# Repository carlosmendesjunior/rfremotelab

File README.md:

# rfremotelab
**RF Remote Laboratory - ReLab**

This is a result of the post-doc of Carlos Mendes Jr. with the research assistance of Lino Van Mulken supported by Rainier van Dommele and idealized by Peter Baltus, all from Eindhoven University of Technology, The Netherlands.

We all hope that this work can help others around the world to disseminate RF laboratory experience among their students from university, college, or school.

We also welcome contributions from everyone! :)

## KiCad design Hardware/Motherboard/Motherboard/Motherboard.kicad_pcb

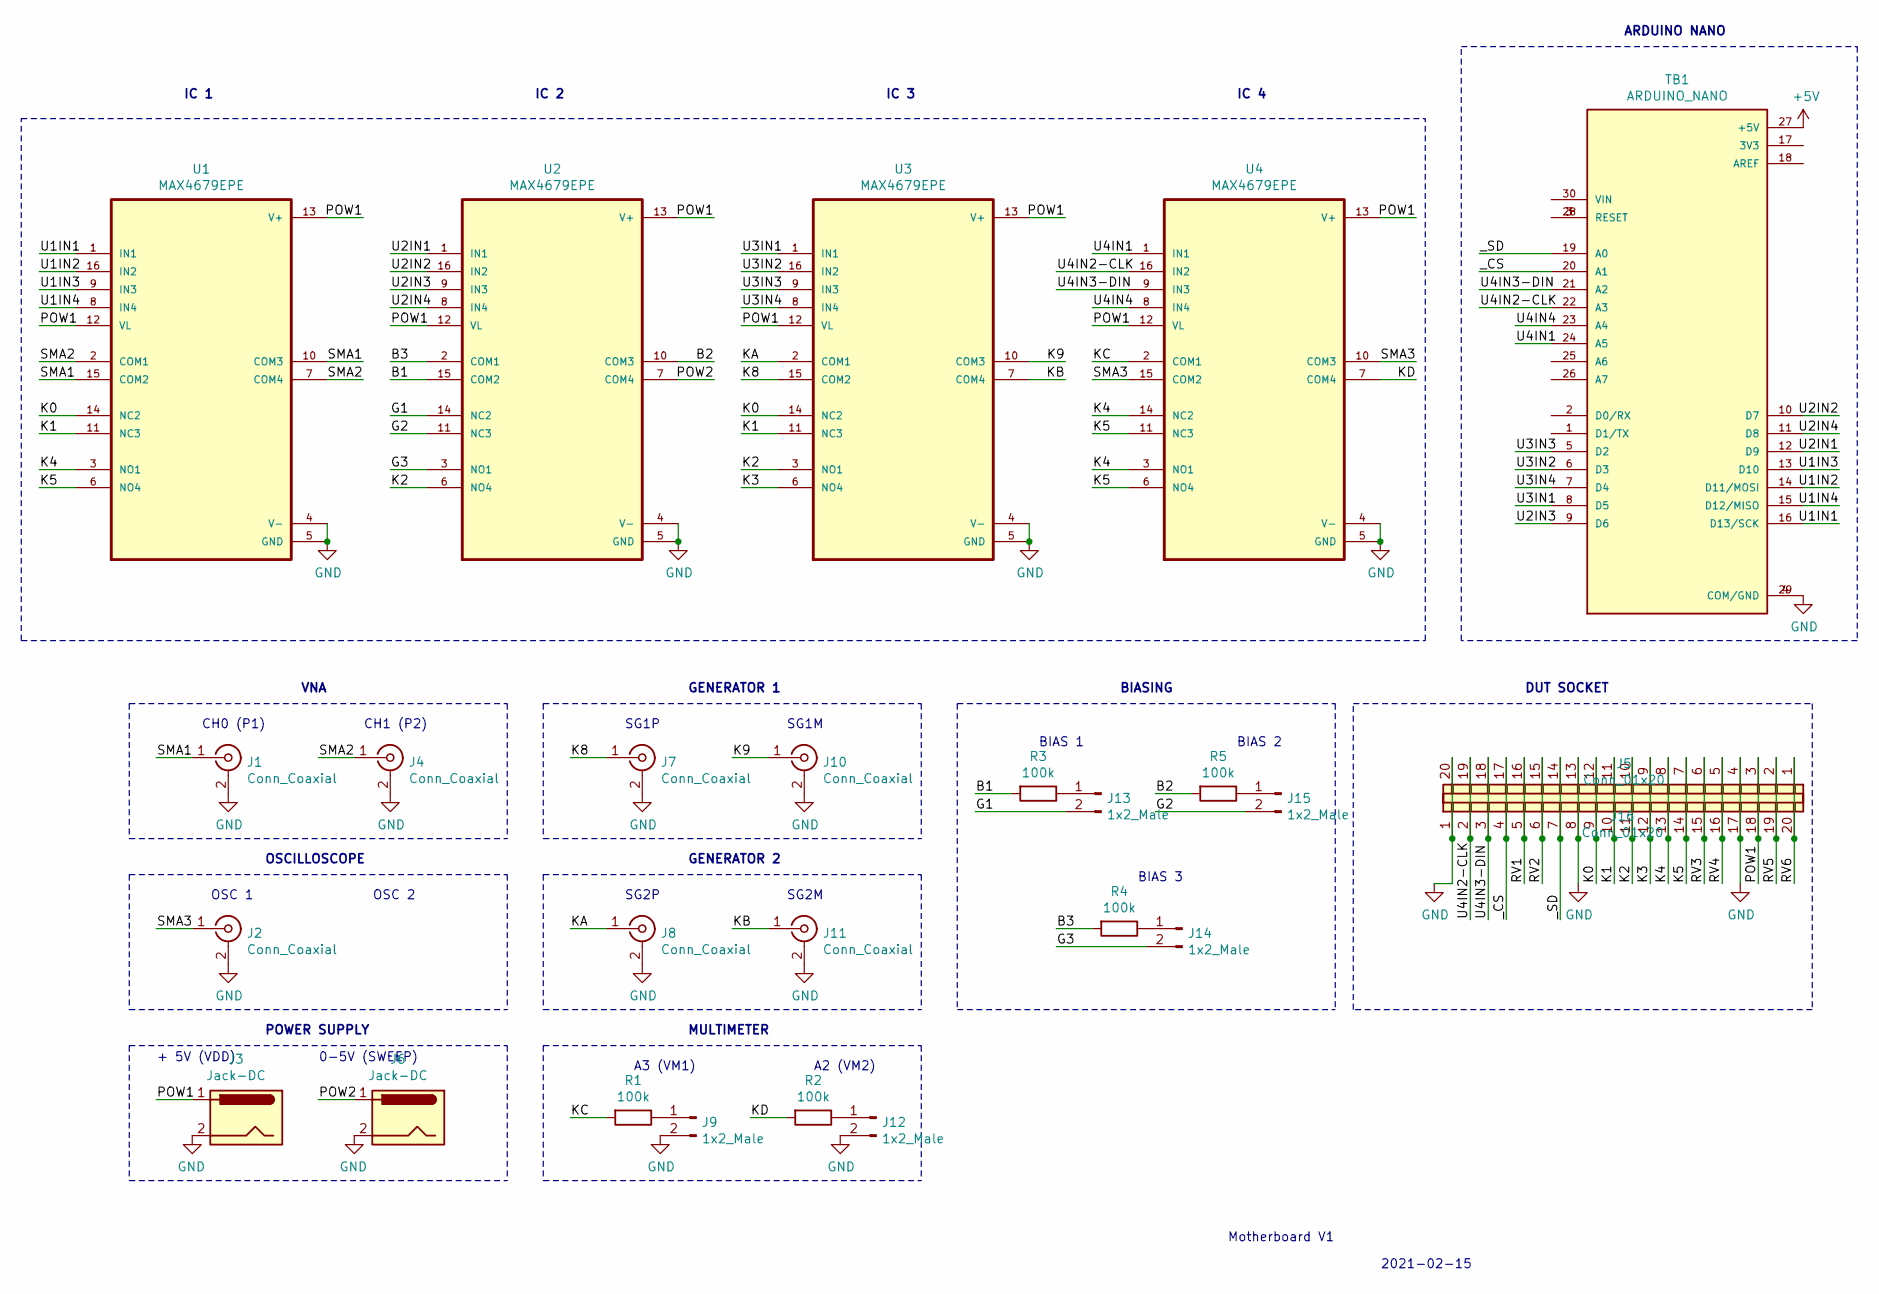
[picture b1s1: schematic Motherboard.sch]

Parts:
J1, J2, J4, J7, J8, J10, J11: Conn_Coaxial; SMA_Amphenol_132289_EdgeMount
J3, J6: Jack-DC; BarrelJack_Wuerth_6941xx301002
J5, J16: Conn_01x20; PinSocket_1x20_P2.54mm_Vertical
J9, J12, J13, J14, J15: 1x2_Male; PinHeader_1x02_P2.54mm_Vertical
R1, R2, R3, R4, R5: 100k; R_Axial_DIN0207_L6.3mm_D2.5mm_P10.16mm_Horizontal
TB1: ARDUINO_NANO; Arduino_Nano
U1, U2, U3, U4: MAX4679EPE; DIP-16_W7.62mm_LongPads

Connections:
+5V: TB1.27 (+5V)
/B1: R3.2, U2.15 (COM2)
/B2: R5.2, U2.10 (COM3)
/B3: R4.2, U2.2 (COM1)
/G1: J13.2, U2.14 (NC2)
/G2: J15.2, U2.11 (NC3)
/G3: J14.2, U2.3 (NO1)
/K0: J5.9, J16.12, U1.14 (NC2), U3.14 (NC2)
/K1: J5.10, J16.11, U1.11 (NC3), U3.11 (NC3)
/K2: J5.11, J16.10, U2.6 (NO4), U3.3 (NO1)
/K3: J5.12, J16.9, U3.6 (NO4)
/K4: J5.13, J16.8, U1.3 (NO1), U4.3 (NO1), U4.14 (NC2)
/K5: J5.14, J16.7, U1.6 (NO4), U4.6 (NO4), U4.11 (NC3)
/K8: J7.1 (In), U3.15 (COM2)
/K9: J10.1 (In), U3.10 (COM3)
/KA: J8.1 (In), U3.2 (COM1)
/KB: J11.1 (In), U3.7 (COM4)
/KC: R1.2, U4.2 (COM1)
/KD: R2.2, U4.7 (COM4)
/POW1: J3.1, J5.18, J16.3, U1.12 (VL), U1.13 (V+), U2.12 (VL), U2.13 (V+), U3.12 (VL), U3.13 (V+), U4.12 (VL), U4.13 (V+)
/POW2: J6.1, U2.7 (COM4)
/RV1: J5.5, J16.16
/RV2: J5.6, J16.15
/RV3: J5.15, J16.6
/RV4: J5.16, J16.5
/RV5: J5.19, J16.2
/RV6: J5.20, J16.1
/SMA1: J1.1 (In), U1.10 (COM3), U1.15 (COM2)
/SMA2: J4.1 (In), U1.2 (COM1), U1.7 (COM4)
/SMA3: J2.1 (In), U4.10 (COM3), U4.15 (COM2)
/U1IN1: TB1.16 (D13/SCK), U1.1 (IN1)
/U1IN2: TB1.14 (D11/MOSI), U1.16 (IN2)
/U1IN3: TB1.13 (D10), U1.9 (IN3)
/U1IN4: TB1.15 (D12/MISO), U1.8 (IN4)
/U2IN1: TB1.12 (D9), U2.1 (IN1)
/U2IN2: TB1.10 (D7), U2.16 (IN2)
/U2IN3: TB1.9 (D6), U2.9 (IN3)
/U2IN4: TB1.11 (D8), U2.8 (IN4)
/U3IN1: TB1.8 (D5), U3.1 (IN1)
/U3IN2: TB1.6 (D3), U3.16 (IN2)
/U3IN3: TB1.5 (D2), U3.9 (IN3)
/U3IN4: TB1.7 (D4), U3.8 (IN4)
/U4IN1: TB1.24 (A5), U4.1 (IN1)
/U4IN2-CLK: J5.2, J16.19, TB1.22 (A3), U4.16 (IN2)
/U4IN3-DIN: J5.3, J16.18, TB1.21 (A2), U4.9 (IN3)
/U4IN4: TB1.23 (A4), U4.8 (IN4)
/_CS: J5.4, J16.17, TB1.20 (A1)
/_SD: J5.7, J16.14, TB1.19 (A0)
GND: J1.2 (Ext), J2.2 (Ext), J3.2, J4.2 (Ext), J5.1, J5.8, J5.17, J6.2, J7.2 (Ext), J8.2 (Ext), J9.2, J10.2 (Ext), J11.2 (Ext), J12.2, J16.4, J16.13, J16.20, TB1.4 (COM/GND), TB1.29 (COM/GND), U1.4 (V-), U1.5 (GND), U2.4 (V-), U2.5 (GND), U3.4 (V-), U3.5 (GND), U4.4 (V-), U4.5 (GND)
unnamed: J9.1, R1.1
unnamed: J12.1, R2.1
unnamed: J13.1, R3.1
unnamed: J14.1, R4.1
unnamed: J15.1, R5.1
unnamed: TB1.3 (RESET), TB1.28 (RESET)

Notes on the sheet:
2021-02-15
Motherboard V1
VNA
CH0 (P1)
CH1 (P2)
OSCILLOSCOPE
OSC 1
OSC 2
GENERATOR 1
SG1P
SG1M
GENERATOR 2
SG2P
SG2M
MULTIMETER
A3 (VM1)
A2 (VM2)
POWER SUPPLY
+ 5V (VDD)
0-5V (SWEEP)
BIASING
ARDUINO NANO
BIAS 1
BIAS 2
BIAS 3
DUT SOCKET
IC 1
IC 2
IC 3
IC 4

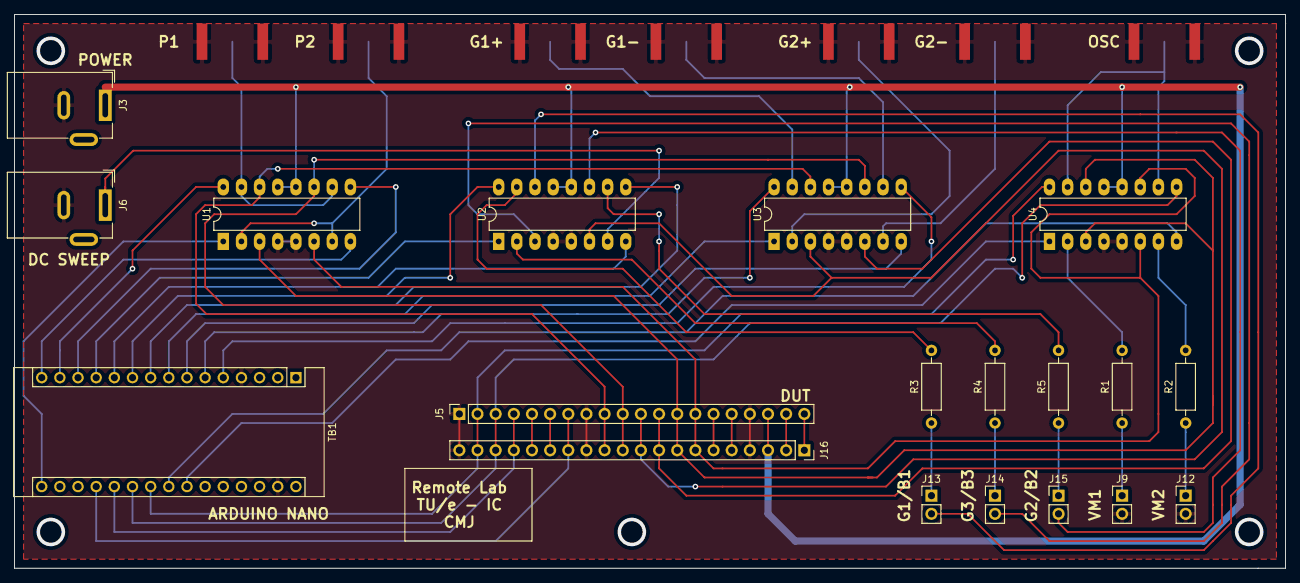
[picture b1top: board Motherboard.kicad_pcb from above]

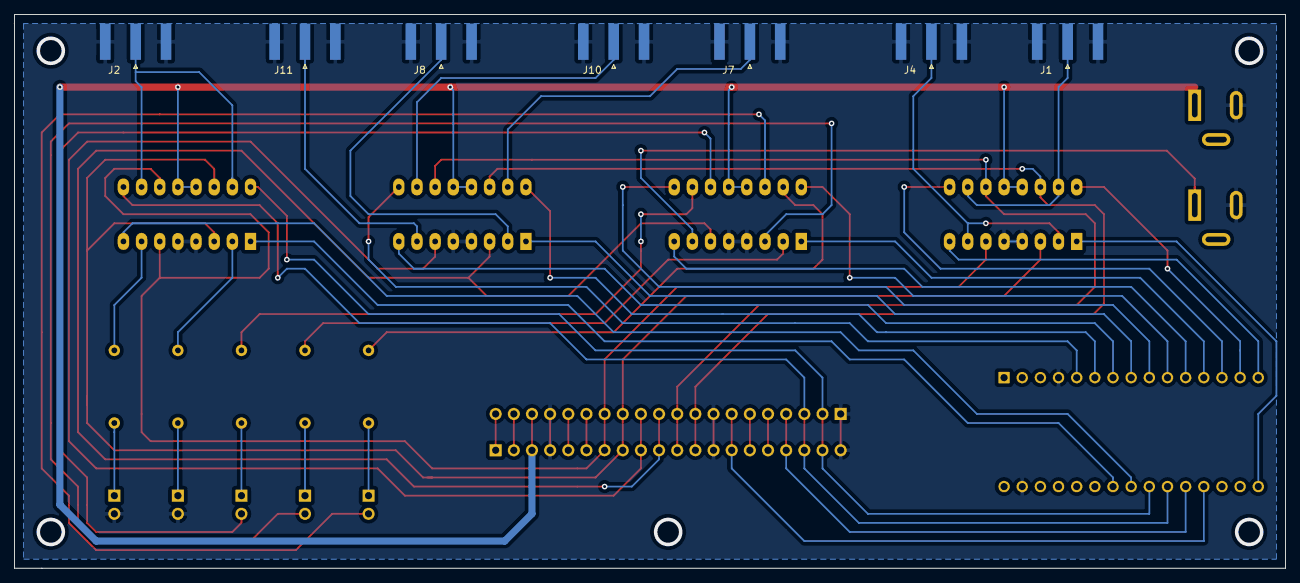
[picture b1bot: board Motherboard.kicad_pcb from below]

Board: 2 copper layers, 177.8 x 77.5 mm, 26 parts (7 on the bottom side), 54 nets.

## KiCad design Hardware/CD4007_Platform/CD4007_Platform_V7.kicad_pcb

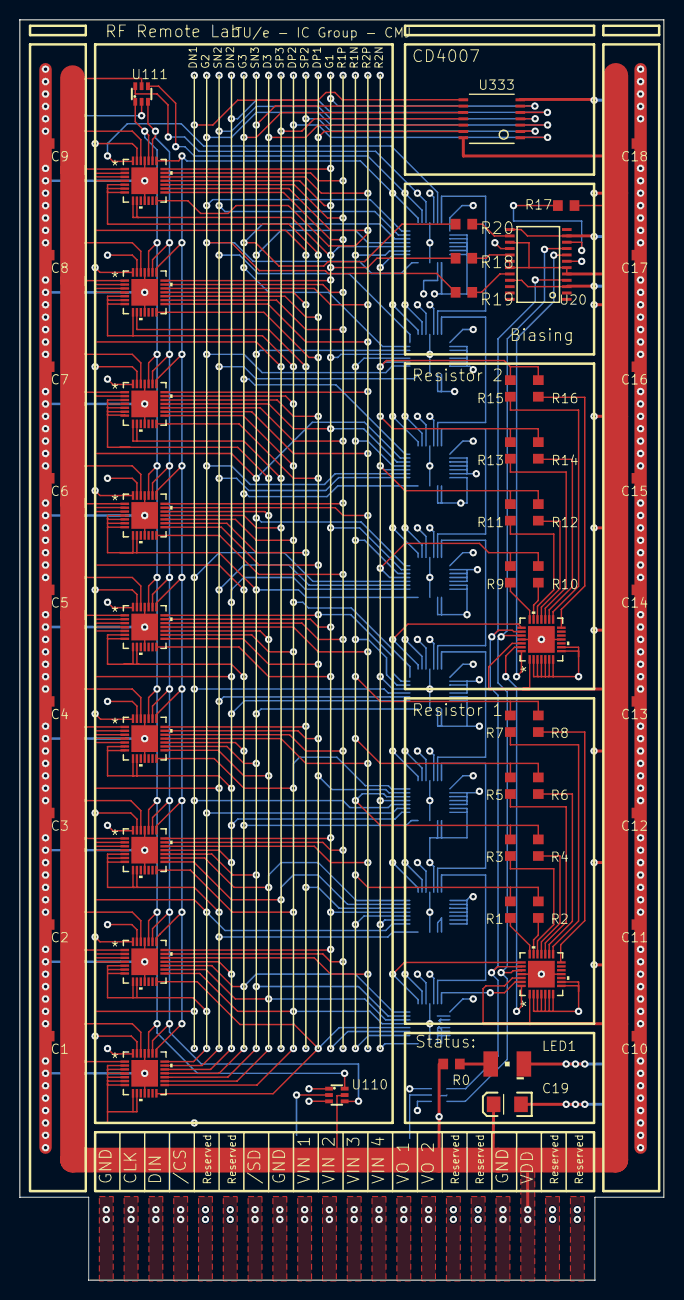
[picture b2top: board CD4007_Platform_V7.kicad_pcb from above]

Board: 4 copper layers, 66.0 x 129.1 mm, 65 parts (0 on the bottom side), 71 nets.

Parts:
C1, C2, C3, C4, C5, C6, C7, C8, C9, C10, C11, C12, C13, C14, C15, C16, C17, C18: C-EUC0603K; C0603K
C19: 10uF; EIA3216
LED1: _T679-?-1E1F1; PLCC2
R0, R1, R2, R3, R4, R5, R6, R7, R8, R9, R10, R11, R12, R13, R14, R15, R16, R17, R18, R19, R20: R-EU_R0603; R0603
U1, U2, U3, U4, U5, U6, U7, U8, U9, U10, U11, U12, U13, U14, U15, U16, U17, U18, U19: MAX14662; QFN-28_UF
U20: AD5204; TSSOP24
U110, U111, U112: 74LVC2G17; SOT363_PHILIPS
U333: CD4007; TSSOP14

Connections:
/CD4007_Platform_V7_2/DO1: U1.28, U2.27
/CD4007_Platform_V7_2/DO2: U2.28, U3.27
/CD4007_Platform_V7_2/DO3: U3.28, U4.27
/CD4007_Platform_V7_2/DO4: U4.28, U5.27
/CD4007_Platform_V7_2/DO5: U5.28, U6.27
/CD4007_Platform_V7_2/DO6: U6.28, U7.27
/CD4007_Platform_V7_2/DO7: U7.28, U8.27
/CD4007_Platform_V7_2/DO8: U8.28, U9.27
/CD4007_Platform_V7_3/DO10: U10.28, U11.27
/CD4007_Platform_V7_3/DO11: U11.28, U12.27
/CD4007_Platform_V7_3/DO12: U12.28, U13.27
/CD4007_Platform_V7_3/DO13: U13.28, U14.27
/CD4007_Platform_V7_3/DO14: U14.28, U15.27
/CD4007_Platform_V7_3/DO15: U15.28, U16.27
/CD4007_Platform_V7_3/DO16: U16.28, U17.27
/CD4007_Platform_V7_3/VI1: U10.2, U10.3, U10.4, U10.5, U10.6, U10.7, U10.8
/CD4007_Platform_V7_3/VI2: U10.9, U11.2, U11.3, U11.4, U11.5, U11.6, U11.7
/CD4007_Platform_V7_3/VI3: U11.8, U11.9, U12.2, U12.3, U12.4, U12.5, U12.6
/CD4007_Platform_V7_3/VI4: U12.7, U12.8, U12.9, U13.2, U13.3, U13.4, U13.5
/CD4007_Platform_V7_3/VO1: U13.6, U13.7, U13.8, U13.9, U14.2, U14.3, U14.4, U14.5
/CD4007_Platform_V7_3/VO2: U14.6, U14.7, U14.8, U14.9, U15.2, U15.3, U15.4, U15.5
/CD4007_Platform_V7_4/DO18: U18.28, U19.27
/CS1: U1.23, U2.23, U3.23, U4.23, U5.23, U6.23, U7.23, U8.23, U9.23, U110.4, U111.3
/CS2: U10.23, U11.23, U12.23, U13.23, U14.23, U15.23, U16.23, U17.23, U111.4, U112.3
/CS3: U18.23, U19.23, U20.4, U112.4
/SD: U1.22, U2.22, U3.22, U4.22, U5.22, U6.22, U7.22, U8.22, U9.22, U10.22, U11.22, U12.22, U13.22, U14.22, U15.22, U16.22, U17.22, U18.22, U19.22, U20.7
CLK1: U1.24, U2.24, U3.24, U4.24, U5.24, U6.24, U7.24, U8.24, U9.24, U110.6, U111.1
CLK2: U10.24, U11.24, U12.24, U13.24, U14.24, U15.24, U16.24, U17.24, U111.6, U112.1
CLK3: U18.24, U19.24, U20.9, U112.6
D3: U1.16, U2.16, U3.16, U4.15, U5.17, U6.19, U7.3, U7.4, U7.5, U7.6, U7.7, U16.21, U17.19, U333.12
DN1: U1.2, U1.3, U1.4, U1.5, U1.6, U1.7, U1.8, U1.9, U2.2, U2.3, U2.4, U13.17, U14.17, U15.17, U333.8
DN2: U1.19, U2.18, U3.18, U4.6, U4.7, U4.8, U4.9, U5.2, U5.3, U5.4, U5.5, U13.15, U14.15, U15.15, U333.5
DO9: U9.28, U10.27
DO17: U17.28, U18.27
DO19: U19.28, U20.8
DP1: U1.14, U2.14, U4.20, U5.15, U5.21, U6.15, U7.14, U7.19, U8.14, U8.17, U9.5, U9.6, U9.7, U14.20, U15.20, U17.17, U333.13
DP2: U1.15, U2.15, U3.14, U4.14, U5.16, U6.17, U7.15, U7.20, U8.5, U8.6, U8.7, U8.8, U14.21, U15.21, U17.18, U333.1
G1: R18.1, U2.21, U3.21, U5.14, U5.20, U7.18, U8.21, U9.8, U9.9, U9.18, U9.21, U10.17, U11.18, U12.19, U13.20, U16.18, U17.16, U333.6
G2: R19.1, U1.21, U2.5, U2.6, U2.7, U2.8, U2.9, U3.2, U3.3, U3.4, U10.14, U10.21, U11.15, U12.16, U15.16, U16.15, U333.3
G3: R20.1, U1.18, U2.17, U4.17, U5.6, U5.7, U5.8, U5.9, U6.2, U6.3, U10.19, U11.20, U12.14, U12.21, U15.14, U17.21, U333.10
unnamed: LED1.A, R0.1
unnamed: R1.1, U18.21
unnamed: R2.1, U18.20
unnamed: R3.1, U18.19
unnamed: R4.1, U18.18
unnamed: R5.1, U18.17
unnamed: R6.1, U18.16
unnamed: R7.1, U18.15
unnamed: R8.1, U18.14
unnamed: R9.1, U19.21
unnamed: R10.1, U19.20
unnamed: R11.1, U19.19
unnamed: R12.1, U19.18
unnamed: R13.1, U19.17
unnamed: R14.1, U19.16
unnamed: R15.1, U19.15
unnamed: R16.1, U19.14
unnamed: R17.1, U20.10
unnamed: R18.2, U20.17
unnamed: R19.2, U20.20
unnamed: R20.2, U20.14
R1N: R1.2, R2.2, R3.2, R4.2, R5.2, R6.2, R7.2, R8.2, U10.16, U11.17, U12.18, U13.19, U14.19, U15.19, U16.17, U17.15
R1P: U2.20, U3.20, U4.19, U5.19, U6.14, U6.21, U7.17, U8.16, U8.20, U9.15, U9.17, U9.20, U18.2, U18.3, U18.4, U18.5, U18.6, U18.7, U18.8, U18.9
R2N: R9.2, R10.2, R11.2, R12.2, R13.2, R14.2, R15.2, R16.2, U10.15, U11.16, U12.17, U13.18, U14.18, U15.18, U16.16, U17.14
R2P: U2.19, U3.19, U4.18, U5.18, U6.20, U7.16, U7.21, U8.15, U8.19, U9.14, U9.16, U9.19, U19.2, U19.3, U19.4, U19.5, U19.6, U19.7, U19.8, U19.9
SN2: U1.20, U3.5, U3.6, U3.7, U3.8, U3.9, U4.2, U4.3, U4.4, U4.5, U10.20, U11.14, U11.21, U12.15, U13.16, U14.16, U16.14, U333.4
SN3: U1.17, U3.17, U4.16, U6.4, U6.5, U6.6, U6.7, U6.8, U6.9, U7.2, U10.18, U11.19, U12.20, U13.14, U13.21, U14.14, U17.20, U333.9
SP2: U4.21, U6.16, U8.9, U8.18, U9.2, U9.3, U9.4, U16.19, U333.2
SP3: U3.15, U6.18, U7.8, U7.9, U8.2, U8.3, U8.4, U16.20, U333.11
VDD: C1.1, C2.1, C3.1, C4.1, C5.1, C6.1, C7.1, C8.1, C9.1, C10.1, C11.1, C12.1, C13.1, C14.1, C15.1, C16.1, C17.1, C18.1, C19.A, R0.2, R17.2, U1.1, U1.26, U2.1, U2.26, U3.1, U3.26, U4.1, U4.26, U5.1, U5.26, U6.1, U6.26, U7.1, U7.26, U8.1, U8.26, U9.1, U9.26, U10.1, U10.26, U11.1, U11.26, U12.1, U12.26, U13.1, U13.26, U14.1, U14.26, U15.1, U15.6, U15.7, U15.8, U15.9, U15.26, U16.1, U16.2, U16.3, U16.4, U16.5, U16.6, U16.7, U16.26, U17.1, U17.26, U18.1, U18.26, U19.1, U19.26, U20.5, U20.6, U20.15, U20.18, U20.19, U110.5, U111.5, U112.5, U333.14
VSS: C1.2, C2.2, C3.2, C4.2, C5.2, C6.2, C7.2, C8.2, C9.2, C10.2, C11.2, C12.2, C13.2, C14.2, C15.2, C16.2, C17.2, C18.2, C19.C, LED1.C, U1.11, U1.25, U1.29, U2.11, U2.25, U2.29, U3.11, U3.25, U3.29, U4.11, U4.25, U4.29, U5.11, U5.25, U5.29, U6.11, U6.25, U6.29, U7.11, U7.25, U7.29, U8.11, U8.25, U8.29, U9.11, U9.25, U9.29, U10.11, U10.25, U10.29, U11.11, U11.25, U11.29, U12.11, U12.25, U12.29, U13.11, U13.25, U13.29, U14.11, U14.25, U14.29, U15.11, U15.25, U15.29, U16.8, U16.9, U16.11, U16.25, U16.29, U17.2, U17.3, U17.4, U17.5, U17.6, U17.7, U17.8, U17.9, U17.11, U17.25, U17.29, U18.11, U18.25, U18.29, U19.11, U19.25, U19.29, U20.3, U20.11, U20.13, U20.16, U20.21, U110.2, U111.2, U112.2, U333.7

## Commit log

2021-11-27 Version 0.1
